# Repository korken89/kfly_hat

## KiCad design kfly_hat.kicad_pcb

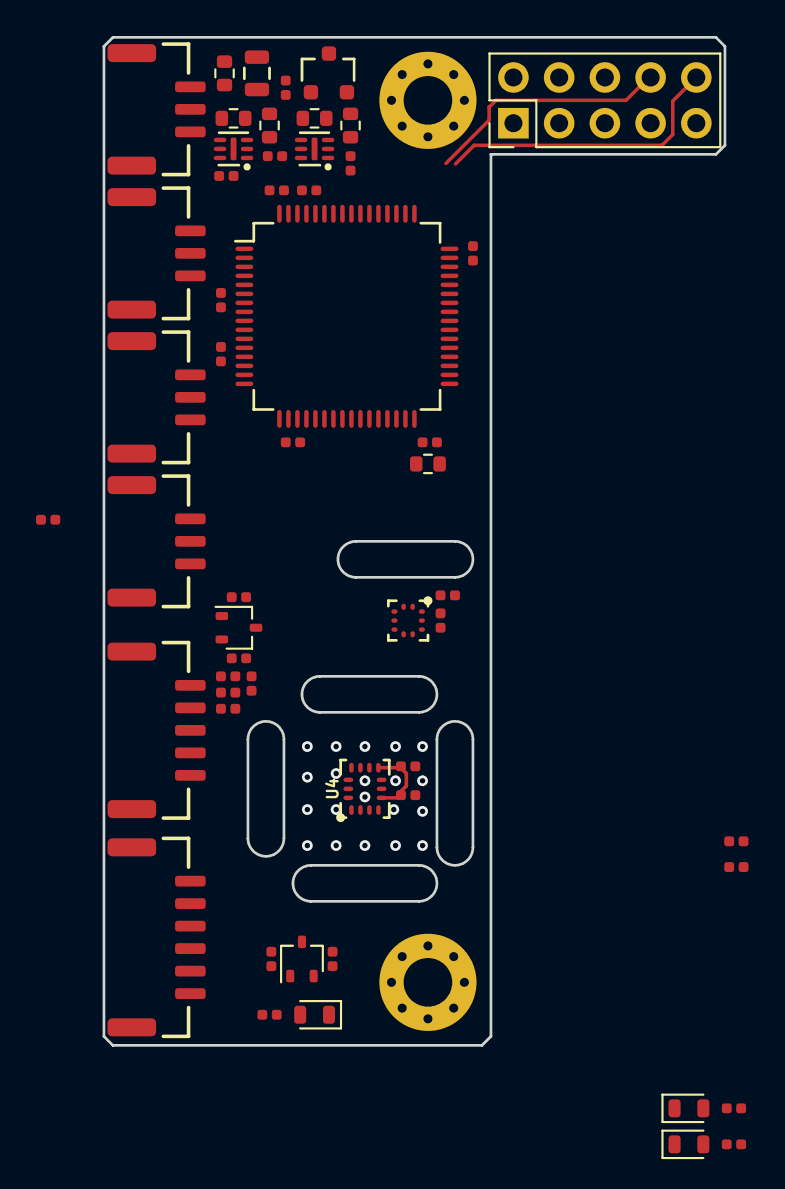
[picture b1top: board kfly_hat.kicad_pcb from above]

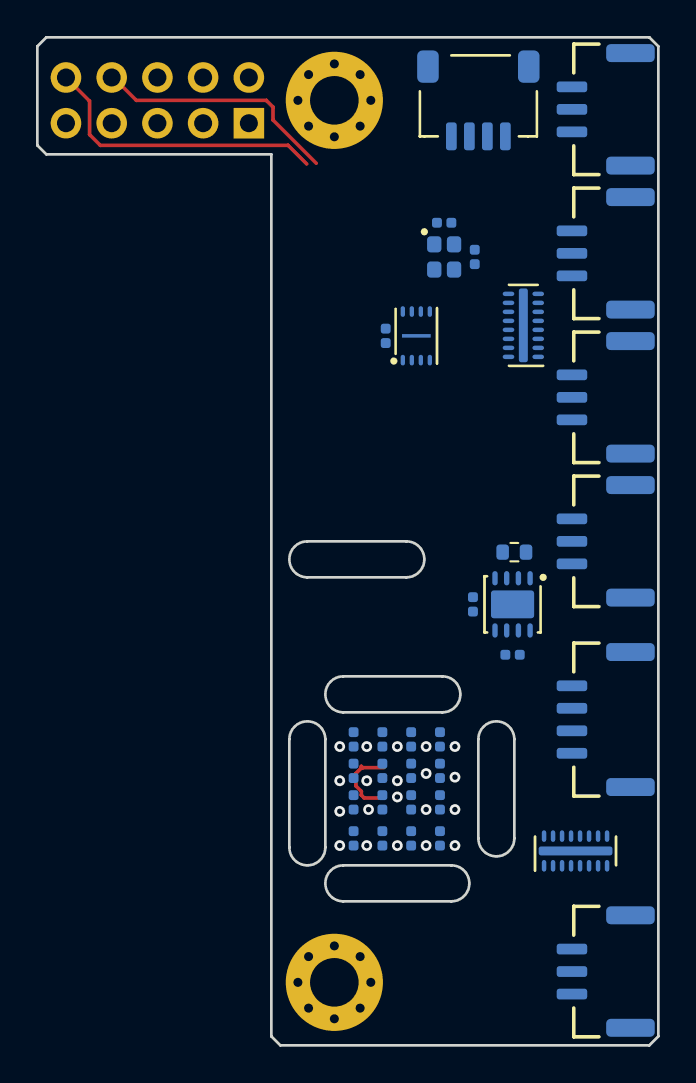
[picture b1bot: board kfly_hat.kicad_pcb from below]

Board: 4 copper layers, 34.5 x 56.0 mm, 90 parts (34 on the bottom side), 79 nets.

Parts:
C1, C2, C3, C4, C5, C8, C9, C10, C14, C15, C16, C17, C18, C20, C22, C23: 0.1uF; C_0402_1005Metric_Rounded
C6, C7, C11, C12, C13, C19, C21: 4.7uF; C_0603_1608Metric_Rounded
D1: SDM40E20LA-7; SOT-23
D2, D3, D4: LED; D_0603_1608Metric_Rounded
F1: 0ZCK0075FF2E; R_0805
J1, J2, J3, J4, J5, J6, J7, J8: KFly_RC_Out; SM03B-GHS-TB
J9: RPi_UART_10pin; PinHeader_2x05_P2.54mm_Vertical
J10: KFly_RC_In; SM03B-GHS-TB
J11: swd-4; jst-sh-hor-4
J12: Dronecode_GPS; SM06B-GHS-TB
J13: Dronecode_CAN; SM04B-GHS-TB
J14: Pixhawk_Switch; SM05B-GHS-TB
MK1, MK2: Mounting_Hole; MountingHole_2.7mm_Pad_Via
Q1, Q2: BC807-25W,115; SOT-323_SC-70
R1, R3, R4, R5, R6, R7, R8, R9, R11, R12, R13, R14, R15, R16, R17, R18, R19, R22, R23, R29, R31: 330; R_0402_1005Metric_Rounded
R2, R20, R25, R27, R30, R33, R34: 10k; R_0402_1005Metric_Rounded
R10, R21, R24, R28, R32: 1k; R_0402_1005Metric_Rounded
R26: 120; R_0402_1005Metric_Rounded
U1: STM32F722RETx; LQFP-64_10x10mm_Pitch0.5mm
U2, U8: NUF8401MNT4G; DFN-16-1EP_1.6x4mm_P0.5mm
U3: BMP388; HLGA-10L-2.0x2.0-BMP388
U4: BMI160; LGA-14-2.5x3
U5: W25X40CLUXIG; USON-8-3x2mm-EP
U6, U7: MIC5318-3.3YMT; DFN-6-1EP_1.6x1.6mm_P0.5mm_EP0.5x1.26mm
U9: TJA1051TK-3; DFN-8-1EP_3x3mm_P0.65mm_EP1.55x2.4mm
X1: SIT8008BI-72-33E-25.000000G; Crystal_4Pin_2.0x1.6mm

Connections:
+3V3: C5.1, C8.1, C12.1, C15.1, C16.1, C17.1, C20.1, C22.2, C23.1, R10.2, R21.2, R33.2, R34.2, U1.1, U1.13, U1.19, U1.32, U1.48, U1.64, U5.3, U5.7, U5.8, U6.4, U9.5, X1.4
+5V: D1.3, F1.2, J9.2, J9.4
+5VP: C11.1, C19.1, F1.1, J10.1, J12.1, J13.1, J14.3, Q1.2, Q2.2, R2.1, R30.2, U9.3
/ARM_BTN_S: C18.2, R28.1, U1.2
/ARM_LED: J14.2, R29.2
/ARM_LED_S: R29.1, U1.15
/BOOT0: R25.1, U1.60
/BUZZER: Q2.1, R30.1, R31.1
/BUZZER_S: R31.2, U1.14
/CANH: J13.2, R26.2, U9.7
/CANL: J13.3, R26.1, U9.6
/CAN_RX: U1.61, U9.4
/CAN_TX: U1.62, U9.1
/COM_RX: J9.10, U8.8
/COM_RX_S: U1.42, U8.9
/COM_TX: J9.8, U8.7
/COM_TX_S: U1.43, U8.10
/CS_BAR: U1.24, U3.6
/CS_IMU: U1.20, U4.12
/FLASH_CS: U1.33, U5.1
/FLASH_MISO: U1.10, U5.2
/FLASH_MOSI: U1.11, U5.5
/FLASH_SCK: U1.34, U5.6
/GPS_RX: J12.3, U8.4
/GPS_RX_S: U1.52, U8.13
/GPS_SCL: J12.4, U8.5
/GPS_SCL_S: R33.1, U1.58, U8.12
/GPS_SDA: J12.5, U8.6
/GPS_SDA_S: R34.1, U1.59, U8.11
/GPS_TX: J12.2, U8.3
/GPS_TX_S: U1.51, U8.14
/HEAT: Q1.3, R3.2, R4.2, R5.2, R6.2, R7.2, R8.2, R9.2, R11.2, R12.2, R13.2, R14.2, R15.2, R16.2, R17.2, R18.2, R19.2, R32.2
/HEAT_ONOFF: R1.1, U1.39
/INT_BAR: U1.35, U3.7
/INT_IMU: U1.36, U4.4
/LED1: R22.1, U1.41
/LED2: R23.1, U1.40
/NRST: C14.1, J11.3, U1.7
/OSC: U1.5, X1.3
/RCOUT_1: J5.1, U2.1
/RCOUT_1_P: U1.50, U2.16
/RCOUT_2: J6.1, U2.2
/RCOUT_2_P: U1.55, U2.15
/RCOUT_3: J7.1, U2.3
/RCOUT_3_P: U1.28, U2.14
/RCOUT_4: J8.1, U2.4
/RCOUT_4_P: U1.29, U2.13
/RCOUT_5: J1.1, U2.5
/RCOUT_5_P: U1.56, U2.12
/RCOUT_6: J2.1, U2.6
/RCOUT_6_P: U1.57, U2.11
/RCOUT_7: J3.1, U2.7
/RCOUT_7_P: U1.25, U2.10
/RCOUT_8: J4.1, U2.8
/RCOUT_8_P: U1.26, U2.9
/RCSBUS: J10.2, U8.2
/RCSBUS_P: U1.17, U8.15
/RCTELEM: J1.2, J2.2, J3.2, J4.2, J5.2, J6.2, J7.2, J8.2, R10.1, U8.1
/RCTELEM_P: U1.38, U8.16
/SENSOR_MISO: U1.22, U3.5, U4.1
/SENSOR_MOSI: U1.23, U3.4, U4.14
/SENSOR_SCK: U1.21, U3.2, U4.13
/SWCLK: J11.1, U1.49
/SWDIO: J11.2, U1.46
/VAA_EN: R20.2, U1.27, U7.1
/VCAP: C21.1, U1.30
GND: C1.2, C2.2, C3.2, C4.2, C5.2, C6.2, C7.2, C8.2, C9.1, C10.1, C11.2, C12.2, C13.2, C14.2, C15.2, C16.2, C17.2, C18.1, C19.2, C20.2, C21.2, C22.1, C23.2, D2.1, D3.1, D4.1, J1.0, J1.3, J2.0, J2.3, J3.0, J3.3, J4.0, J4.3, J5.0, J5.3, J6.0, J6.3, J7.0, J7.3, J8.0, J8.3, J9.6, J9.9, J10.0, J10.3, J11.4, J12.0, J12.6, J13.0, J13.4, J14.0, J14.4, R3.1, R4.1, R5.1, R6.1, R7.1, R8.1, R9.1, R11.1, R12.1, R13.1, R14.1, R15.1, R16.1, R17.1, R18.1, R19.1, R20.1, R24.1, R25.2, R27.2, U1.12, U1.18, U1.31, U1.47, U1.63, U2.17, U3.3, U3.8, U3.9, U4.6, U4.7, U5.4, U6.2, U6.7, U7.2, U7.7, U8.17, U9.2, U9.8, U9.9, X1.2
unnamed: C6.1, D1.1, U6.1, U6.3
unnamed: C7.1, D1.2, U7.3
unnamed: C9.2, U6.6
unnamed: C10.2, U7.6
unnamed: D2.2, R22.2
unnamed: D3.2, R23.2
unnamed: D4.2, R32.1
unnamed: J14.1, R27.1, R28.2
unnamed: J14.5, Q2.3
unnamed: Q1.1, R1.2, R2.2
unnamed: R21.1, X1.1
VAA: C1.1, C2.1, C3.1, C4.1, C13.1, R24.2, U3.1, U3.10, U4.5, U4.8, U7.4

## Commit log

2018-04-23 More schematic
2018-04-23 Started PCB
2018-04-24 More PCB
